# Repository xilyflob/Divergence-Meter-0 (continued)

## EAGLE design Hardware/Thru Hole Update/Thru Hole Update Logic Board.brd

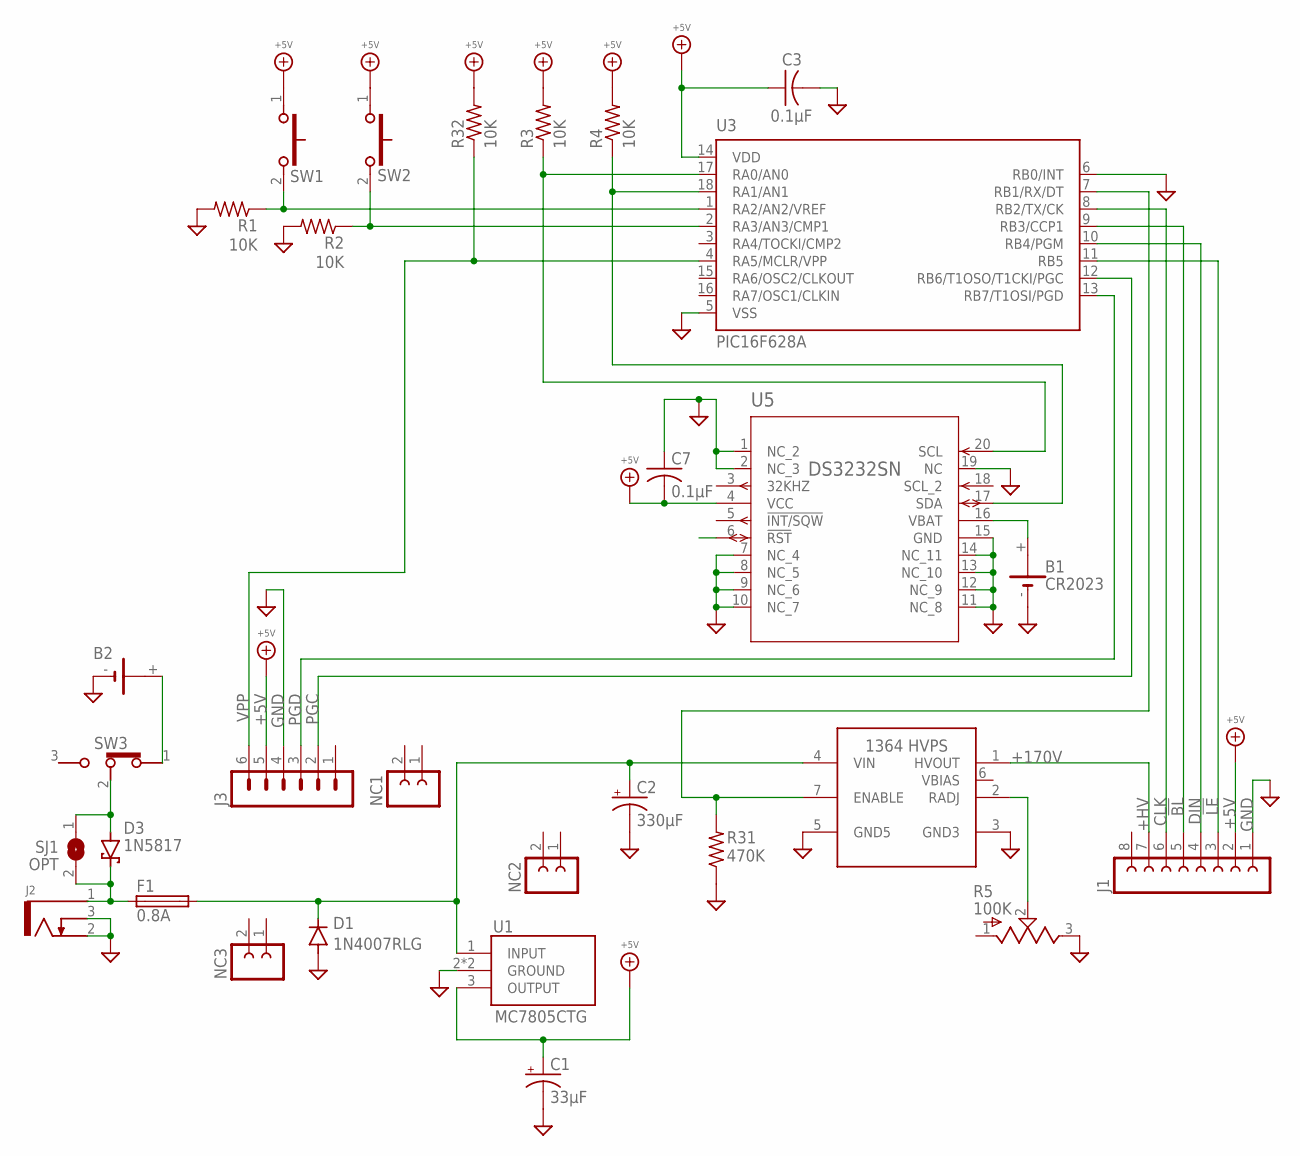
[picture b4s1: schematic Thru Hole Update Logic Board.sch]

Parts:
B1: CR2023; 103
B2: BATTERYWIRE_ATTACH; 1291
C1: 33μF; E2-5
C2: 330µF; E3,5-8
C3: 0.1µF; C025-040X050
C7: 0.1µF; C0805
D1: 1N4007RLG; DO41-7
D3: 1N5817; DO41-7
F1: 0.8A; 5X20MM
J1: FE08
J2: KLDX-0202-B; KDLX-0202-X
J3: MA06
NC1, NC2, NC3: FE02
R1, R2, R3, R4, R32: 10K; 0207/10
R5: 100K; PV37W
R31: 470K; 0207/10
SJ1: OPT; SJ
SW1, SW2: FSMRA4JH04; FSMRA4JH
SW3: 5MS1S102AM6QES; SLIDE_SPDT_MINI
U1: MC7805CTG; TO-220-3_RA
U2: 1364-HVPS-H
U3: PIC16F628A; DIP-18
U5: DS3232SN; SOIC-20

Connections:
!BL!: J1.5, U3.9 (RB3/CCP1)
!LE!: J1.3, U3.11 (RB5)
+5V: C1.+, C3.1, C7.2, J1.2, J3.5, R3.2, R4.2, R32.2, SW1.1, SW2.1, U1.3 (OUTPUT), U3.14 (VDD), U5.4 (VCC)
+9V: D3.C, F1.1A (1), F1.1B (1), J2.1, SJ1.2
+9V_1: C2.+, D1.C, F1.2A (2), F1.2B (2), U1.1 (INPUT), U2.4 (VIN)
+9V_2: D3.A, SJ1.1, SW3.2 (COM)
+9V_4: B2.+, SW3.1 (POS_1)
+HV: J1.7, U2.1 (HVOUT)
BAT: B1.+, U5.16 (VBAT)
CLK: J1.6, U3.8 (RB2/TX/CK)
DIN: J1.4, U3.10 (RB4/PGM)
ENABLE: R31.2, U2.7 (ENABLE), U3.7 (RB1/RX/DT)
GND: B1.-, B2.-, C1.-, C2.-, C3.2, C7.1, D1.A, J1.1, J2.2, J2.3, J3.4, R1.2, R2.2, R5.3, R31.1, U1.2 (GROUND), U1.2_1 (GROUND), U2.3 (GND3), U2.5 (GND5), U3.5 (VSS), U3.6 (RB0/INT), U5.1 (NC_2), U5.2 (NC_3), U5.7 (NC_4), U5.8 (NC_5), U5.9 (NC_6), U5.10 (NC_7), U5.11 (NC_8), U5.12 (NC_9), U5.13 (NC_10), U5.14 (NC_11), U5.15 (GND), U5.19 (NC)
MYSTERY_3: U5.6 (!RST)
PGC: J3.2, U3.12 (RB6/T1OSO/T1CKI/PGC)
PGD: J3.3, U3.13 (RB7/T1OSI/PGD)
RADJ: R5.2, U2.2 (RADJ)
SCL: R3.1, U3.17 (RA0/AN0), U5.20 (SCL)
SDA: R4.1, U3.18 (RA1/AN1), U5.17 (SDA)
SW1: R1.1, SW1.2, U3.1 (RA2/AN2/VREF)
SW2: R2.1, SW2.2, U3.2 (RA3/AN3/CMP1)
VPP: J3.6, R32.1, U3.4 (RA5/MCLR/VPP)

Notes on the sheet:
+170V

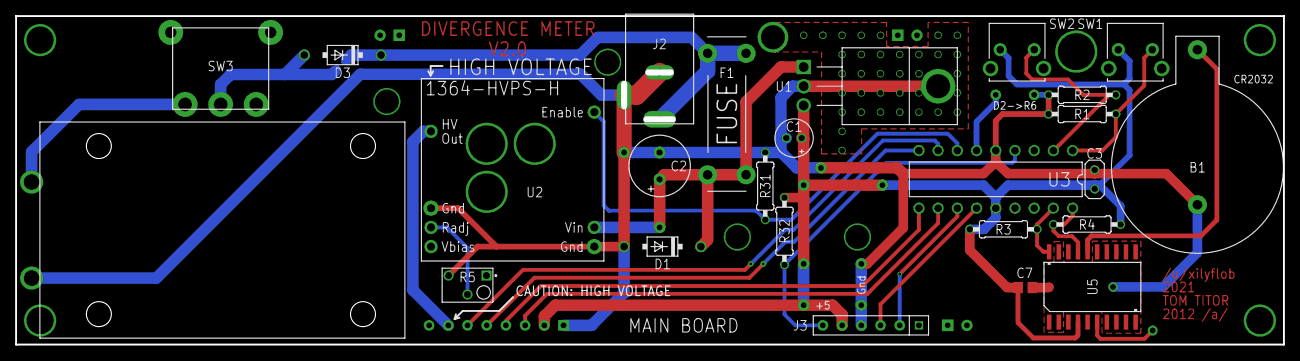
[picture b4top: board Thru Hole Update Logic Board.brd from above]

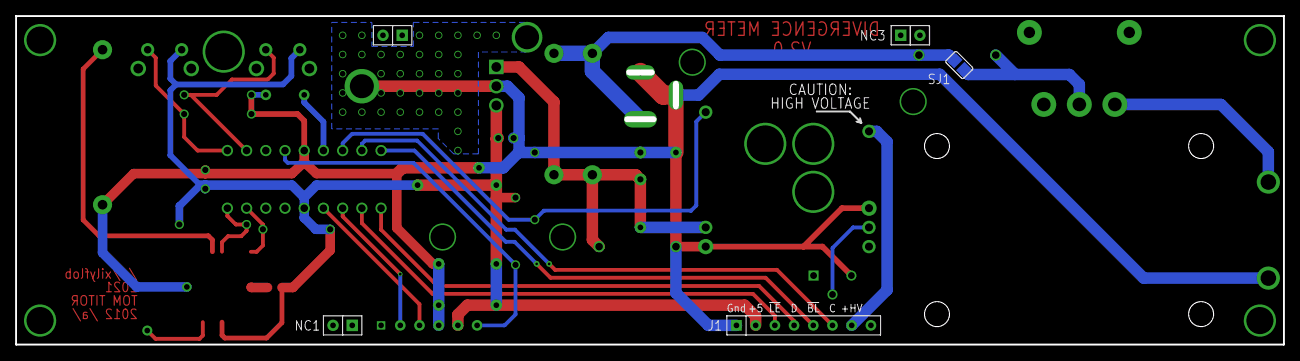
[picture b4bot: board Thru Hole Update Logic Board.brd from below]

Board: 2 copper layers, 167.6 x 43.4 mm, 30 parts (5 on the bottom side), 21 nets.

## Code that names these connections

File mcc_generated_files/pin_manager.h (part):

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// get/set RA2_UNUSED aliases
#define RA2_UNUSED_TRIS                 TRISAbits.TRISA2
#define RA2_UNUSED_LAT                  LATAbits.LATA2
#define RA2_UNUSED_PORT                 PORTAbits.RA2
#define RA2_UNUSED_WPU                  WPUAbits.WPUA2
#define RA2_UNUSED_OD                   ODCONAbits.ODCA2
#define RA2_UNUSED_ANS                  ANSELAbits.ANSA2
#define RA2_UNUSED_SetHigh()            do { LATAbits.LATA2 = 1; } while(0)
#define RA2_UNUSED_SetLow()             do { LATAbits.LATA2 = 0; } while(0)
#define RA2_UNUSED_Toggle()             do { LATAbits.LATA2 = ~LATAbits.LATA2; } while(0)
#define RA2_UNUSED_GetValue()           PORTAbits.RA2
#define RA2_UNUSED_SetDigitalInput()    do { TRISAbits.TRISA2 = 1; } while(0)
#define RA2_UNUSED_SetDigitalOutput()   do { TRISAbits.TRISA2 = 0; } while(0)
#define RA2_UNUSED_SetPullup()          do { WPUAbits.WPUA2 = 1; } while(0)
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// get/set RA5_UNUSED aliases
#define RA5_UNUSED_TRIS                 TRISAbits.TRISA5
#define RA5_UNUSED_LAT                  LATAbits.LATA5
#define RA5_UNUSED_PORT                 PORTAbits.RA5
#define RA5_UNUSED_WPU                  WPUAbits.WPUA5
#define RA5_UNUSED_OD                   ODCONAbits.ODCA5
#define RA5_UNUSED_ANS                  ANSELAbits.ANSA5
#define RA5_UNUSED_SetHigh()            do { LATAbits.LATA5 = 1; } while(0)
#define RA5_UNUSED_SetLow()             do { LATAbits.LATA5 = 0; } while(0)
#define RA5_UNUSED_Toggle()             do { LATAbits.LATA5 = ~LATAbits.LATA5; } while(0)
#define RA5_UNUSED_GetValue()           PORTAbits.RA5
#define RA5_UNUSED_SetDigitalInput()    do { TRISAbits.TRISA5 = 1; } while(0)
#define RA5_UNUSED_SetDigitalOutput()   do { TRISAbits.TRISA5 = 0; } while(0)
#define RA5_UNUSED_SetPullup()          do { WPUAbits.WPUA5 = 1; } while(0)
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#define RB4_SetHigh()            do { LATBbits.LATB4 = 1; } while(0)
#define RB4_SetLow()             do { LATBbits.LATB4 = 0; } while(0)
#define RB4_Toggle()             do { LATBbits.LATB4 = ~LATBbits.LATB4; } while(0)
#define RB4_GetValue()              PORTBbits.RB4
#define RB4_SetDigitalInput()    do { TRISBbits.TRISB4 = 1; } while(0)
#define RB4_SetDigitalOutput()   do { TRISBbits.TRISB4 = 0; } while(0)
#define RB4_SetPullup()             do { WPUBbits.WPUB4 = 1; } while(0)
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// get/set RB5_UNUSED aliases
#define RB5_UNUSED_TRIS                 TRISBbits.TRISB5
#define RB5_UNUSED_LAT                  LATBbits.LATB5
#define RB5_UNUSED_PORT                 PORTBbits.RB5
#define RB5_UNUSED_WPU                  WPUBbits.WPUB5
#define RB5_UNUSED_OD                   ODCONBbits.ODCB5
#define RB5_UNUSED_ANS                  ANSELBbits.ANSB5
#define RB5_UNUSED_SetHigh()            do { LATBbits.LATB5 = 1; } while(0)
#define RB5_UNUSED_SetLow()             do { LATBbits.LATB5 = 0; } while(0)
#define RB5_UNUSED_Toggle()             do { LATBbits.LATB5 = ~LATBbits.LATB5; } while(0)
#define RB5_UNUSED_GetValue()           PORTBbits.RB5
#define RB5_UNUSED_SetDigitalInput()    do { TRISBbits.TRISB5 = 1; } while(0)
#define RB5_UNUSED_SetDigitalOutput()   do { TRISBbits.TRISB5 = 0; } while(0)
#define RB5_UNUSED_SetPullup()          do { WPUBbits.WPUB5 = 1; } while(0)
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#define RB6_SetHigh()            do { LATBbits.LATB6 = 1; } while(0)
#define RB6_SetLow()             do { LATBbits.LATB6 = 0; } while(0)
#define RB6_Toggle()             do { LATBbits.LATB6 = ~LATBbits.LATB6; } while(0)
#define RB6_GetValue()              PORTBbits.RB6
#define RB6_SetDigitalInput()    do { TRISBbits.TRISB6 = 1; } while(0)
#define RB6_SetDigitalOutput()   do { TRISBbits.TRISB6 = 0; } while(0)
#define RB6_SetPullup()             do { WPUBbits.WPUB6 = 1; } while(0)
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// get/set RB7_UNUSED aliases
#define RB7_UNUSED_TRIS                 TRISBbits.TRISB7
#define RB7_UNUSED_LAT                  LATBbits.LATB7
#define RB7_UNUSED_PORT                 PORTBbits.RB7
#define RB7_UNUSED_WPU                  WPUBbits.WPUB7
#define RB7_UNUSED_OD                   ODCONBbits.ODCB7
#define RB7_UNUSED_ANS                  ANSELBbits.ANSB7
#define RB7_UNUSED_SetHigh()            do { LATBbits.LATB7 = 1; } while(0)
#define RB7_UNUSED_SetLow()             do { LATBbits.LATB7 = 0; } while(0)
#define RB7_UNUSED_Toggle()             do { LATBbits.LATB7 = ~LATBbits.LATB7; } while(0)
#define RB7_UNUSED_GetValue()           PORTBbits.RB7
#define RB7_UNUSED_SetDigitalInput()    do { TRISBbits.TRISB7 = 1; } while(0)
#define RB7_UNUSED_SetDigitalOutput()   do { TRISBbits.TRISB7 = 0; } while(0)
#define RB7_UNUSED_SetPullup()          do { WPUBbits.WPUB7 = 1; } while(0)
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// get/set SW1 aliases
#define SW1_TRIS                 TRISCbits.TRISC0
#define SW1_LAT                  LATCbits.LATC0
#define SW1_PORT                 PORTCbits.RC0
#define SW1_WPU                  WPUCbits.WPUC0
#define SW1_OD                   ODCONCbits.ODCC0
#define SW1_ANS                  ANSELCbits.ANSC0
#define SW1_SetHigh()            LATCbits.LATC0 = 1
#define SW1_SetLow()             LATCbits.LATC0 = 0
#define SW1_Toggle()             LATC ^= 0b00000001
#define SW1_GetValue()           PORTCbits.RC0
#define SW1_SetDigitalInput()    TRISCbits.TRISC0 = 1
#define SW1_SetDigitalOutput()   TRISCbits.TRISC0 = 0
#define SW1_SetPullup()          WPUCbits.WPUC0 = 1
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// get/set SW2 aliases
#define SW2_TRIS                 TRISCbits.TRISC1
#define SW2_LAT                  LATCbits.LATC1
#define SW2_PORT                 PORTCbits.RC1
#define SW2_WPU                  WPUCbits.WPUC1
#define SW2_OD                   ODCONCbits.ODCC1
#define SW2_ANS                  ANSELCbits.ANSC1
#define SW2_SetHigh()            LATCbits.LATC1 = 1
#define SW2_SetLow()             LATCbits.LATC1 = 0
#define SW2_Toggle()             LATC ^= 0b00000010
#define SW2_GetValue()           PORTCbits.RC1
#define SW2_SetDigitalInput()    TRISCbits.TRISC1 = 1
#define SW2_SetDigitalOutput()   TRISCbits.TRISC1 = 0
#define SW2_SetPullup()          WPUCbits.WPUC1 = 1
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// get/set CLK aliases
#define CLK_TRIS                 TRISCbits.TRISC3
#define CLK_LAT                  LATCbits.LATC3
#define CLK_PORT                 PORTCbits.RC3
#define CLK_WPU                  WPUCbits.WPUC3
#define CLK_OD                   ODCONCbits.ODCC3
#define CLK_ANS                  ANSELCbits.ANSC3
#define CLK_SetHigh()            LATCbits.LATC3 = 1
#define CLK_SetLow()             LATCbits.LATC3 = 0
#define CLK_Toggle()             LATC ^= 0b00001000
#define CLK_GetValue()           PORTCbits.RC3
#define CLK_SetDigitalInput()    TRISCbits.TRISC3 = 1
#define CLK_SetDigitalOutput()   TRISCbits.TRISC3 = 0
#define CLK_SetPullup()          WPUCbits.WPUC3 = 1
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// get/set BL aliases
#define BL_TRIS                 TRISCbits.TRISC4
#define BL_LAT                  LATCbits.LATC4
#define BL_PORT                 PORTCbits.RC4
#define BL_WPU                  WPUCbits.WPUC4
#define BL_OD                   ODCONCbits.ODCC4
#define BL_ANS                  ANSELCbits.ANSC4
#define BL_SetHigh()            LATCbits.LATC4 = 1
#define BL_SetLow()             LATCbits.LATC4 = 0
#define BL_Toggle()             LATC ^= 0b00010000
#define BL_GetValue()           PORTCbits.RC4
#define BL_SetDigitalInput()    TRISCbits.TRISC4 = 1
#define BL_SetDigitalOutput()   TRISCbits.TRISC4 = 0
#define BL_SetPullup()          WPUCbits.WPUC4 = 1
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// get/set DIN aliases
#define DIN_TRIS                 TRISCbits.TRISC5
#define DIN_LAT                  LATCbits.LATC5
#define DIN_PORT                 PORTCbits.RC5
#define DIN_WPU                  WPUCbits.WPUC5
#define DIN_OD                   ODCONCbits.ODCC5
#define DIN_ANS                  ANSELCbits.ANSC5
#define DIN_SetHigh()            LATCbits.LATC5 = 1
#define DIN_SetLow()             LATCbits.LATC5 = 0
#define DIN_Toggle()             LATC ^= 0b00100000
#define DIN_GetValue()           PORTCbits.RC5
#define DIN_SetDigitalInput()    TRISCbits.TRISC5 = 1
#define DIN_SetDigitalOutput()   TRISCbits.TRISC5 = 0
#define DIN_SetPullup()          WPUCbits.WPUC5 = 1
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// get/set LE aliases
#define LE_TRIS                 TRISCbits.TRISC6
#define LE_LAT                  LATCbits.LATC6
#define LE_PORT                 PORTCbits.RC6
#define LE_WPU                  WPUCbits.WPUC6
#define LE_OD                   ODCONCbits.ODCC6
#define LE_ANS                  ANSELCbits.ANSC6
#define LE_SetHigh()            LATCbits.LATC6 = 1
#define LE_SetLow()             LATCbits.LATC6 = 0
#define LE_Toggle()             LATC ^= 0b01000000
#define LE_GetValue()           PORTCbits.RC6
#define LE_SetDigitalInput()    TRISCbits.TRISC6 = 1
#define LE_SetDigitalOutput()   TRISCbits.TRISC6 = 0
#define LE_SetPullup()          WPUCbits.WPUC6 = 1
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// get/set HVPS_ENABLE aliases
#define HVPS_ENABLE_TRIS                 TRISCbits.TRISC7
#define HVPS_ENABLE_LAT                  LATCbits.LATC7
#define HVPS_ENABLE_PORT                 PORTCbits.RC7
#define HVPS_ENABLE_WPU                  WPUCbits.WPUC7
#define HVPS_ENABLE_OD                   ODCONCbits.ODCC7
#define HVPS_ENABLE_ANS                  ANSELCbits.ANSC7
#define HVPS_ENABLE_SetHigh()            LATCbits.LATC7 = 1
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
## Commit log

2021-06-04 Create Software
2021-06-04 First software upload
2021-06-13 Original board rebuild added
    Added the Eagle files for the original Tom Titor PCBs that have been remade in the new software.
2021-06-13 Create Notes.md
    Some notes about the rebuilt version
2021-06-13 Library mismatch fix
    Major errors involved with a late change that was made to the component library. Don't let your layout and schematic get out of sync kids.
2021-06-14 Thru hole design update version added
2021-06-14 Some helpful info for programming
2021-06-15 Clock program split part 1
    Renaming the project files for the DS3232 version of the software. 8803 version will be forthcoming soonish.
2021-06-30 Clock program split part 2
    Uploaded the 8803 version of the software. Updated the version number in the DS3232 version. Also uploaded the original files from Tom Titor for completeness
2021-08-01 SMT designs and data sheets
    Some data sheets and the SMT designs as they stand, because oh god HELP MEH!
2021-08-08 Component numbering fix
    There was a gap from U3 to U5, shifted U5 onwards down one (eg to U4).
    Was also playing the with DR for JLCPCB, some pads etc may be wonky because of this.
2021-09-04 Conversion of Eagle to KiCad for 8803
    Imported to KiCad and tweaked to fix issues from that.
2022-05-30 Out of date file removal
    I've decided to abandon/delete the eagle versions of the rebuild. They are so hideously out of date that they are of little use at this point. I am also unlikely to ever go back into eagle to fix the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
2022-05-30 Update some info files
2022-11-16 Progress update and archive
2022-11-22 Software V1.10
    Update 8803 software to 1.10, also removed the DS3232 as part of the scope reduction
2022-11-26 Logic Rev. A Hardware Update
